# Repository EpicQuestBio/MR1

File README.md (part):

# MR1 Nanopore Reader (MR1)

[-brightgreen.svg)](#testing--verification)

The **MR1 Nanopore Reader** is an open-source, ultra-low-noise solid-state and biological nanopore sequencer flow cell, low-current transimpedance amplifier, and automated fluidic control system. It integrates high-precision parametric CAD models (`build123d`), ultra-low-leakage analog front-end electronics (KiCad), an automated dual-pump fluidic handler, and an ESP32-S3 high-speed continuous streaming firmware stack.

## Architecture & Overview
The system uses a complete **4-electrode topology** (Working Electrode `WE_POS` / `>PORE_AMP`, Working Sense `WS_CIS` & `WS_CIS_WIDE`, Reference Electrode `RE_TRANS`, Counter Electrode `CE_GNDA`) combined with explicitly driven guards (`GUARD`, `GUARD_WIDE`, `GUARD_CIS_A`, `GUARD_CIS_B`) across a distributed 12-pin interface ($36\text{ mm}$ span) to achieve sub-picoampere sensitivity, neutralize stray capacitance, and distribute mechanical spring forces across the PTFE substrate.

The architecture consists of:
- **Headstage Hardware**: A custom, low-parasitic PTFE/Rogers interposer cartridge that seats a 4x4mm nanopore wafer clamped within silicone PDMS gaskets. It interfaces via gold-plated pogo pins to a low-bias-current transimpedance amplifier (LMP7721) mounted beneath the flowcell.
- **Reader Hardware (MR1)**: An ESP32-S3-driven core processing node operating a continuous 100 kHz SPI DMA data acquisition sequence, dual DACs for precision transmembrane voltage bias, and USB CDC-ACM streaming logic.
- **Pump / Power Subsystem**: A dedicated USB-PD powered board managing automated fluidic dispensing (peristaltic motors), pressure sensing, and SBU-based I2C communication back to the main MR1 host.
- **Data Ingestion Pipeline**: High-throughput IPC software utilizing python scripts (`daq_client.py`) and zeroMQ / WebSocket endpoints to reliably process, structure, decode, and log the real-time electrical data for machine learning basecalling or browser visualization.

## Setup & Prerequisites
To build, modify, or interact with this repository, ensure your environment meets these requirements.

### Toolchain Prerequisites
- **Python**: 3.10+
- **KiCad**: Version 7.0+ (For PCB design modifications and scripting exports)
- **PlatformIO Core (CLI)**: For firmware compilation (`pio run`)
- **OpenSCAD / build123d**: For generating solid body parts.
- **Node.js**: v18+ (For UI and test automation dependencies)

### Environment Setup
Run the bootstrap setup scripts depending on your OS to establish a clean python virtual environment and node module cache.
```bash
# On Linux/macOS
./setup_env.sh

# On Windows (PowerShell)
.\setup_env.ps1
```

Activate the python virtual environment:
```bash
source .venv/bin/activate
```

### Build & Test
You can trigger the comprehensive unit, integration, and dimension-parity tests using the included test suite.
```bash
# Ensure you have activated the virtual environment and built assets
python run_tests.py
# Or directly via pytest
pytest tests/
```

To build and upload firmware to the MR1 reader or the Pump board:
```bash
# Navigate to the target directory
cd MR1_firmware  # or cd Pump_firmware
pio run --target upload
```

## License

This project is dedicated to the public domain under the **CC0 1.0 Universal (CC0 1.0) Public Domain Dedication**.

Created by Lawrence R. Kincheloe III / Molecular Reality Corp (2026).
See the `LICENSE` file for the full text.

---

## Table of Contents

- [Architecture & Overview](#architecture--overview)
- [Setup & Prerequisites](#setup--prerequisites)
- [License](#license)
- [System Architecture](#system-architecture)
- [Project Structure](#project-structure)
- [Quick Start & Environment Setup](#quick-start--environment-setup)
- [Deliverables & Export System](#deliverables--export-system)
- [Hardware Build Pipeline & Board Status](#hardware-build-pipeline--board-status)
- [OpenAuto-CFD & Co-Design](#openauto-cfd--co-design)
- [3D Visualizer & Interactive Inspection](#3d-visualizer--interactive-inspection)
- [KiCad Action Plugin & CLI](#kicad-action-plugin--cli)
- [Testing & Verification](#testing--verification)
- [Hardware & Electronics](#hardware--electronics)
- [ESP32-S3 Firmware](#esp32-s3-firmware)
- [Fluidic Routing & Mold Casting](#fluidic-routing--mold-casting)
- [Documentation Index](#documentation-index)

## System Architecture

```
                       +---------------------------------------+
                       |           Host PC / Laptop            |
                       |  (High-Throughput Binary Telemetry)   |
                       +-------------------+-------------------+
                                           | J1_HOST (USB-C Cable: USB-PD Sink + High-Speed Data)
                                           v
                       +---------------------------------------+
                       |      Pump Module Board (Pump/)        |
                       |  - STUSB4500 Autonomous USB-PD Sink   |
                       |  - TS3USB221 USB 2.0 Streaming Pass   |
                       |  - STM32G431 Control MCU @ 170 MHz    |
                       |  - Dual Honeywell ABP2 Pressure Sens  |
                       |  - Dual DRV8837C Peristaltic Drivers  |
                       |  - Clean Regulated 5V Output Filter   |
                       +-------------------+-------------------+
                                           | J2_MR1 (USB-C Link: +5V_MR1_CLEAN + SBU I2C + USB)
                                           v
                       +---------------------------------------+
                       |         ESP32-S3 MCU (MR1)            |
                       |  Core 1: ADC SPI DMA & USB CDC Stream |
                       |  Core 0: Web Server, Leak & Pump Ctrl |
                       +---------+-------------------+---------+
                                 |                   |
            SPI Bus (100 kHz)    |                   | UART (J22) / SBU I2C
                                 v                   v
     +-----------------------------+        +--------------------------+
     |     AD40xx 16/18-Bit ADC    |        |  Dual Peristaltic Pumps  |
     |   LMP7721 Ultra-Low-Noise   |        |  (Cis & Trans Chambers)  |
     |     Cartridge Amplifier     |        +--------------------------+
     +--------------+--------------+
                    | Gold Pogo Pins (Ultra-low noise shielded)
                    v
     +---------------------------------------------------------+
     |              Hexagonal Cartridge Flow Cell              |
     |  - Cis & Trans Fluidic Chambers ('X' microfluidic)      |
     |  - Cast Silicone Gasket with Nanopore Silicon Wafer     |
     |  - M75x8mm Clamping Torque Cap & Pressure Puck          |
     |  - Conductive Weep Moat / Leak Detection Sensor         |
     +---------------------------------------------------------+
```

---

## Project Structure

```
mr1/
├── src/                          # Parametric CAD models (build123d / Python)
│   ├── cartridge.py              # Flow cell cartridge stack & PCB models
│   ├── housing.py                # Reader and Pump housings, lids, mounting
│   ├── nanopore_wafer_mold.py    # Interlocking two-part resin casting mold
│   ├── torque_cap.py             # M75/M76 ratcheting torque limiter cap
│   ├── adapters.py               # Luer-lock and threaded NPT fluidic adapters
│   ├── connectors.py             # USB-C, JST XH, and bulkhead panel mounts
│   ├── assembly.py               # Full 3D assembly & 3D spline routing sweeps
│   ├── collision_check.py        # Automated 3D BREP collision & clearance checker
│   └── constants.py              # Central engineering & physical parameters
├── MR1/                          # KiCad 10.0 project for Main Reader Board (4-Layer)
├── Amplifier/                    # KiCad 10.0 project for Cartridge Transimpedance Amp (2-Layer)
├── Pump/                         # KiCad 10.0 project for Pump Controller & USB-PD Hub (4-Layer)
├── MR1_firmware/                 # ESP32-S3 C++ firmware (PlatformIO)
│   ├── include/                  # Pinout mapping, binary protocol framing, web portal
│   ├── src/hal/                  # AD40xx SPI DMA ADC, MCP4822 DAC, Leak Detector
│   ├── src/comm/                 # High-speed USB CDC streaming & UART Pump protocol
│   └── src/web/                  # Embedded Web Portal with WebSocket Oscilloscope
├── wiring/                       # WireViz electrical and fluidic harness specs
│   ├── reader_wiring.yaml        # USB-C, motor, and analog pogo wiring harnesses
│   └── reader_tubing.yaml        # FEP, PharMed BPT, and silicone fluidic tubing specs
├── tests/                        # Automated unit, CAD bounds, firmware, and E2E tests
│   ├── test_geometry.py          # Geometric validity and collision regression
│   ├── test_golden_stl_bounds.py # Dimensional assertions against golden models
│   ├── test_connector_bounds.py  # Connector mounting dimensional checks
│   ├── test_firmware_protocol.py # Binary framing, CRC-16, and DAC mapping tests
│   └── test_exports_e2e.py       # Full deliverables validation (141 files)
├── scripts/                      # Build, export, and testing automation
│   ├── export_manager.py         # Universal multi-domain export orchestrator
│   ├── export_all.sh             # POSIX bash export runner
│   └── run_e2e_tests.sh          # POSIX bash end-to-end test runner
├── exports/                      # Generated release deliverables & manifest
├── requirements.txt              # Pinned Python virtual environment dependencies
├── setup_env.sh                  # Virtual environment manager (Linux/macOS/Bash)
├── setup_env.ps1                 # Virtual environment manager (Windows PowerShell)
├── Makefile                      # Standard project build and export targets
├── EXPORTS.md                    # Detailed deliverables and ordering documentation
├── BOM.md                        # Mechanical bill of materials & sourcing links
└── CASTING.md                    # PDMS/Silicone flow cell casting guidelines
```

---

## Quick Start & Environment Setup

### 1. Initialize Python Virtual Environment

The project uses a local virtual environment (`.venv`) for all Python CAD generation, export pipelines, and test suites.

**On Windows (PowerShell):**
```powershell
.\setup_env.ps1
```

**On Linux / macOS / Git Bash:**
```bash
chmod +x setup_env.sh install.sh
./setup_env.sh
```

To verify environment health at any time:
```bash
./setup_env.sh --check        # or powershell -File .\setup_env.ps1 -Check
```

### 2. Required External Tools (Optional for specific export domains)
- **KiCad 10.0 CLI** (`kicad-cli`): Required to generate Gerbers, Drill files, Pick & Place CSVs, BOMs, and PDF schematics.
- **Graphviz** (`dot`): Required by WireViz for rendering graphical wiring and tubing diagrams.
- **PlatformIO Core** (`pio`): Required to compile ESP32-S3 firmware binaries.

---

## Deliverables & Export System

The repository features an automated multi-domain export orchestrator (`scripts/export_manager.py`) managed via GNU Make, shell scripts, or npm:

### Common Commands

```bash
# Export all project deliverables (CAD, KiCad, Wiring, Firmware, and Manifest)
make export

# Or export specific domains
make export-cad        # 3D Solids (STEP/STL) & 2D CNC Profiles (DXF)
make export-kicad      # Gerbers, Drill, POS, BOM, and PDF schematics
make export-wiring     # WireViz wiring harness and fluidic diagrams
make export-firmware   # Compile and stage ESP32-S3 firmware binaries

# Verify manifest and deliverables
make check             # Verify all 141 indexed deliverables exist on disk
make test              # Run unit tests and CAD collision clearance checks
make test-e2e          # Run end-to-end deliverables validation test
```

### Generated Deliverables Inventory (`exports/`)
- **30 STL Meshes**: Ready for 3D printing (SLA resin molds, TPU pusher plates, PETG housings, and PTFE interposer models).
- **22 STEP Models**: Parametric BREP solids for mechanical assembly and CAD exchange.
- **13 DXF Profiles**: 2D profiles for CNC milling polypropylene sheet stock and synchronizing KiCad PCB `Edge.Cuts` (including `Interposer_DXF.dxf` and `Plate_2_Channel_DXF.dxf`).
- **Fab-Ready PCB Archives**: `MR1_Gerbers.zip` (4-layer main board) and `Amplifier_Gerbers.zip` (2-layer amplifier).
- **Manufacturing Documentation**: Pick-and-Place (POS) coordinates, BOM CSVs, and multi-sheet schematic PDFs.
- **Harness Documentation**: WireViz diagrams for internal wiring and 1/8" barb fluidic tubing.
- **ESP32-S3 Firmware**: Staged `firmware.bin`, `bootloader.bin`, and `partitions.bin`.
- **SHA-256 Manifest**: `exports/manifest.json` tracks file sizes and cryptographic hashes for all 159 files for drift detection.

See [EXPORTS.md](EXPORTS.md) for full details and PCB fabrication recommendations.

---

## Hardware Build Pipeline & Board Status

Automated code scanners and reviewers sometimes mistake the repository's PCB source files for static production-ready layouts. The MR1 hardware design pipeline relies on two fundamental principles:

1. **Dynamic Artifact Generation**:
   The `.kicad_pcb` layout files and downstream fabrication deliverables (Gerber layers, NC drill files, BOMs, Pick and Place POS files, multi-sheet PDF schematics) are dynamically generated and reconciled via the repository's automation pipeline (`scripts/export_manager.py`, Python footprint/layout generators, and `kicad-cli`), rather than being maintained as static hand-edited binaries in the working tree.

2. **Current Board Layout & Routing Status**:
   - **`MR1` Main Reader Board** (`MR1/`): 111 footprints placed, placement complete, 0 routed copper tracks.
   - **`Amplifier` Cartridge Board** (`Amplifier/`): 48 footprints placed, placement complete, 0 routed copper tracks.
   - **`Interposer` Microfluidic Board** (`Interposer/`): 33 footprints placed, 9 routed segments.
   - **`Pump` Controller Board** (`Pump/`): 18 footprints placed, procedurally generated stubs — STM32 QFN-48 currently a 1-pad stub with passives and 3D models pending per [`TODO.md`](TODO.md) §22.

For details on Gerber archiving, dynamic export workflows, and hardware version tags, see the [Artifact & Gerber Release Policy in EXPORTS.md](EXPORTS.md#artifact--gerber-release-policy).

---

## OpenAuto-CFD & Co-Design

The **MR1 Nanopore Reader** incorporates the **OpenAuto-CFD** co-design framework ([`openauto.project.json`](openauto.project.json) / [`atlas.project.json`](atlas.project.json)) to bridge Electrical CAD (KiCad), Mechanical CAD (Build123d / OpenSCAD), and Microfluidic Multiphysics into a single automated pipeline.

### Why OpenAuto-CFD?
Nanopore sensing demands precise hydrodynamic and electro-chemical alignment:
1. **Laminar Stokes Flow ($\text{Re} \ll 1$):** With $50\,\mu\text{m} \times 25\,\mu\text{m}$ channels and $10\,\mu\text{L/min}$ delivery, OpenAuto-CFD calculates viscous pressure drops ($\Delta P \approx 6.2\text{ kPa}$) and eliminates turbulent vortex formation.
2. **SiN Membrane Burst Safety:** Free-standing $20\text{ nm}$ silicon nitride membranes rupture at differential pressures $\Delta P_{\text{burst}} \sim 10\text{ mbar}$. OpenAuto-CFD co-simulation balances hydrodynamic resistance across Cis and Trans chambers to prevent wafer fracture.
3. **Dead-Volume & Bubble Prevention:** Eliminates stagnation recirculation zones ($\vec{v} < 0.01 \cdot v_{\text{bulk}}$) that trap air microbubbles or cause analyte sample carryover.
4. **Concentric Kelvin Cell Coupling:** Aligns the 4-electrode Kelvin sensing array on the PTFE interposer directly with the microfluidic chamber aperture.

See the comprehensive [OpenAuto-CFD Guide](docs/OPENAUTO_CFD.md) for full physical derivations and co-simulation specs.

---

## 3D Visualizer & Interactive Inspection

The repository provides a rich multi-layer 3D visualizer powered by `build123d` and `ocp_viewer`:

```bash
# Launch interactive 3D assembly visualizer
npm run visualize
# Or via Python directly:
python src/assembly.py

# Or launch via install script diagnostic flag:
./install.sh --viewer
```

### Visualizer Features
- **Full System Assembly:** Displays the Peristaltic Pump base module, Reader Housing & Tower, 4× Luer Bulkhead Panel Mounts, 7-layer Cartridge Stack (Bottom Pusher Plate, Base Hex Plate, Fitted Gasket, Active PCB, Wafer Gasket, Top Hex Plate, Pressure Puck), and Torque-Lock Cap.
- **3D Swept Tubing Routes:** Renders actual 3D splines for all 5 fluidic paths (`TUBE_PUMP`, `TUBE_FEED`, `TUBE_TRANS_LINE`, `TUBE_WASTE_1`, `TUBE_WASTE_2`) with verified bend radii.
- **X-Ray & Clipping Plane Inspection:** Enables cross-sectional slicing to verify internal gasket compression and pogo pin deflection.
- **WireViz Electrical & Tubing Harnesses:** Generates SVG and HTML diagrams for internal wiring (`wiring/reader_wiring.yaml`) and fluid lines (`wiring/reader_tubing.yaml`) via `npm run export:wiring`.
- **Automated 360° Flythrough Video:** Renders photorealistic rotating orbits using PyVista VTK via `npm run render:flythrough`.

---

## KiCad Action Plugin & CLI

The repository includes a dedicated KiCad Action Plugin and CLI verification engine ([`plugins/openauto_cfd_plugin.py`](plugins/openauto_cfd_plugin.py)) ensuring PCB layouts strictly comply with mechanical, fluidic, and manifest constraints.

### How to Install the Plugin into KiCad
```bash
# Install plugin into active KiCad installation (~/.local/share/kicad/ or %APPDATA%/kicad/)
npm run openauto:install-plugin
# Or via Python:
python plugins/openauto_cfd_plugin.py --install
```

### Using Inside KiCad PCB Editor (GUI)
1. Open any board (`Amplifier.kicad_pcb`, `MR1.kicad_pcb`, `Pump.kicad_pcb`, or `Interposer.kicad_pcb`).
2. Navigate to **Tools $\to$ External Plugins $\to$ OpenAuto-CFD: Co-Design & Clearance Verifier**.
3. The plugin parses the board, checks Edge.Cuts continuity, verifies bounding dimensions against `openauto.project.json`, and displays a comprehensive verification report.

### Standalone CLI & CI/CD Verification
```bash
# Validate all 4 boards in headless mode (Edge.Cuts continuity, dimensions, and net mapping)
npm run openauto:validate

# Synchronize Edge.Cuts dimensions back into the openauto.project.json manifest
npm run openauto:sync
```

---

## Testing & Verification

The project enforces zero physical interference and strict dimensional fidelity across all hardware interfaces:

```bash
# Run the complete test suite (Unit Tests, Collision Checks, Firmware Protocol, Parity, and E2E)
python run_tests.py
```

### Automated Validation Includes:
1. **Golden STL & PCB Bounds**: Asserts dimensions of all generated CAD models against benchmark constraints.
2. **BREP Collision Clearance (6 Independent Suites)**:
   - Cartridge stack component alignment.
   - Housing and lid clearances.
   - M75×8mm external / M76×8mm internal helical thread engagement (0 interference volume).
   - PCB standoff clearances against fluidic lines.
   - Internal component clearance (wiring vs. cartridge solids).
   - Flexible routing collision sweeps against module envelopes.
3. **Spline Bend Radius Validation**: Computes instantaneous curvature along swept routes and verifies compliance with minimum bend radii (Silicone/FEP tubing $\ge 10\text{ mm}$, Wiring $\ge 10\text{ mm}$).
4. **CAD Feature Validation Suite**: Validates 80x60mm rectangular motherboard, hexagonal carrier frame, circular nanopore carrier, mold modes, lid cutouts, and pump case bosses.
5. **Firmware Protocol Tests**: CRC-16 integrity, binary packet serialization (`StreamFrame`), pump packet XOR checksums, and DAC voltage-to-code mapping.
6. **E2E Deliverables Tests**: Validates headers, non-zero file sizes, and SHA-256 hashes of all 159 export deliverables.

---

## Hardware & Electronics

- **MR1 Main Controller Board** (`MR1/`):
  - 4-Layer stackup:
    - Layer 1 (Top Signal): Component placement, USB D+/D-, SPI traces to FPC, DAC outputs
    - Layer 2 (Ground Plane): Split into GNDA (Quiet Analog Ground) and GND (Digital Ground)
    - Layer 3 (Power Plane): Split into Analog Power (VDDA, VSSA) and Digital Power (+3V3, VBUS)
    - Layer 4 (Bottom Signal): Secondary routing, low-speed housekeeping, and auxiliary pours
  - ESP32-S3-MINI-1U MCU with native high-speed USB CDC.
  - Dedicated SPI bus for high-speed ADC sampling.
  - Dual MCP4822 12-bit DACs providing bipolar pore bias voltages (-1.587V to +1.587V) and unblocking pulses.
  - Conductive weep-hole leak detection sensing on GPIO1.
- **PTFE Interposer Circuit Board** (`Interposer/` & `src/cartridge.py`):
  - 55.0 × 51.962 × 0.8 mm hexagonal substrate fabricated on ultra-low-loss PTFE / Rogers RO4350B.
  - Physical and electrical barrier dividing Cis (top) and Trans (bottom) microfluidic chambers.
  - Dual-sided silver chloride (Ag/AgCl) ribbon electrode pads positioned inside the Cis ($30^\circ$) and Trans ($210^\circ$) flow channels.
  - Central 6.20 × 6.20 mm diamond cutout ($45^\circ$) allowing the silicone gasket protrusion to seal directly around the silicon nanopore wafer.
  - 12-pin guarded ENIG landing array (`PogoPin_Target_12Pin_Distributed`) flanking high-impedance sense lines (`WS_CIS`, `RE_TRANS`) with driven low-impedance `GUARD` pins.
  - Hermetically clamped between `Cast_Nanopore_Wafer_Gasket` (top) and `Fitted_Amplifier_Gasket` (bottom).
- **Cartridge Transimpedance Amplifier** (`Amplifier/`):
  - 2-Layer 0.8 mm ultra-thin board designed for direct insertion into the flow cell stack.
  - LMP7721 ultra-low input bias current amplifier (sub-femtoampere leakage).
  - Low-leakage guard rings and driven shields guarding the high-impedance nanopore input node.
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
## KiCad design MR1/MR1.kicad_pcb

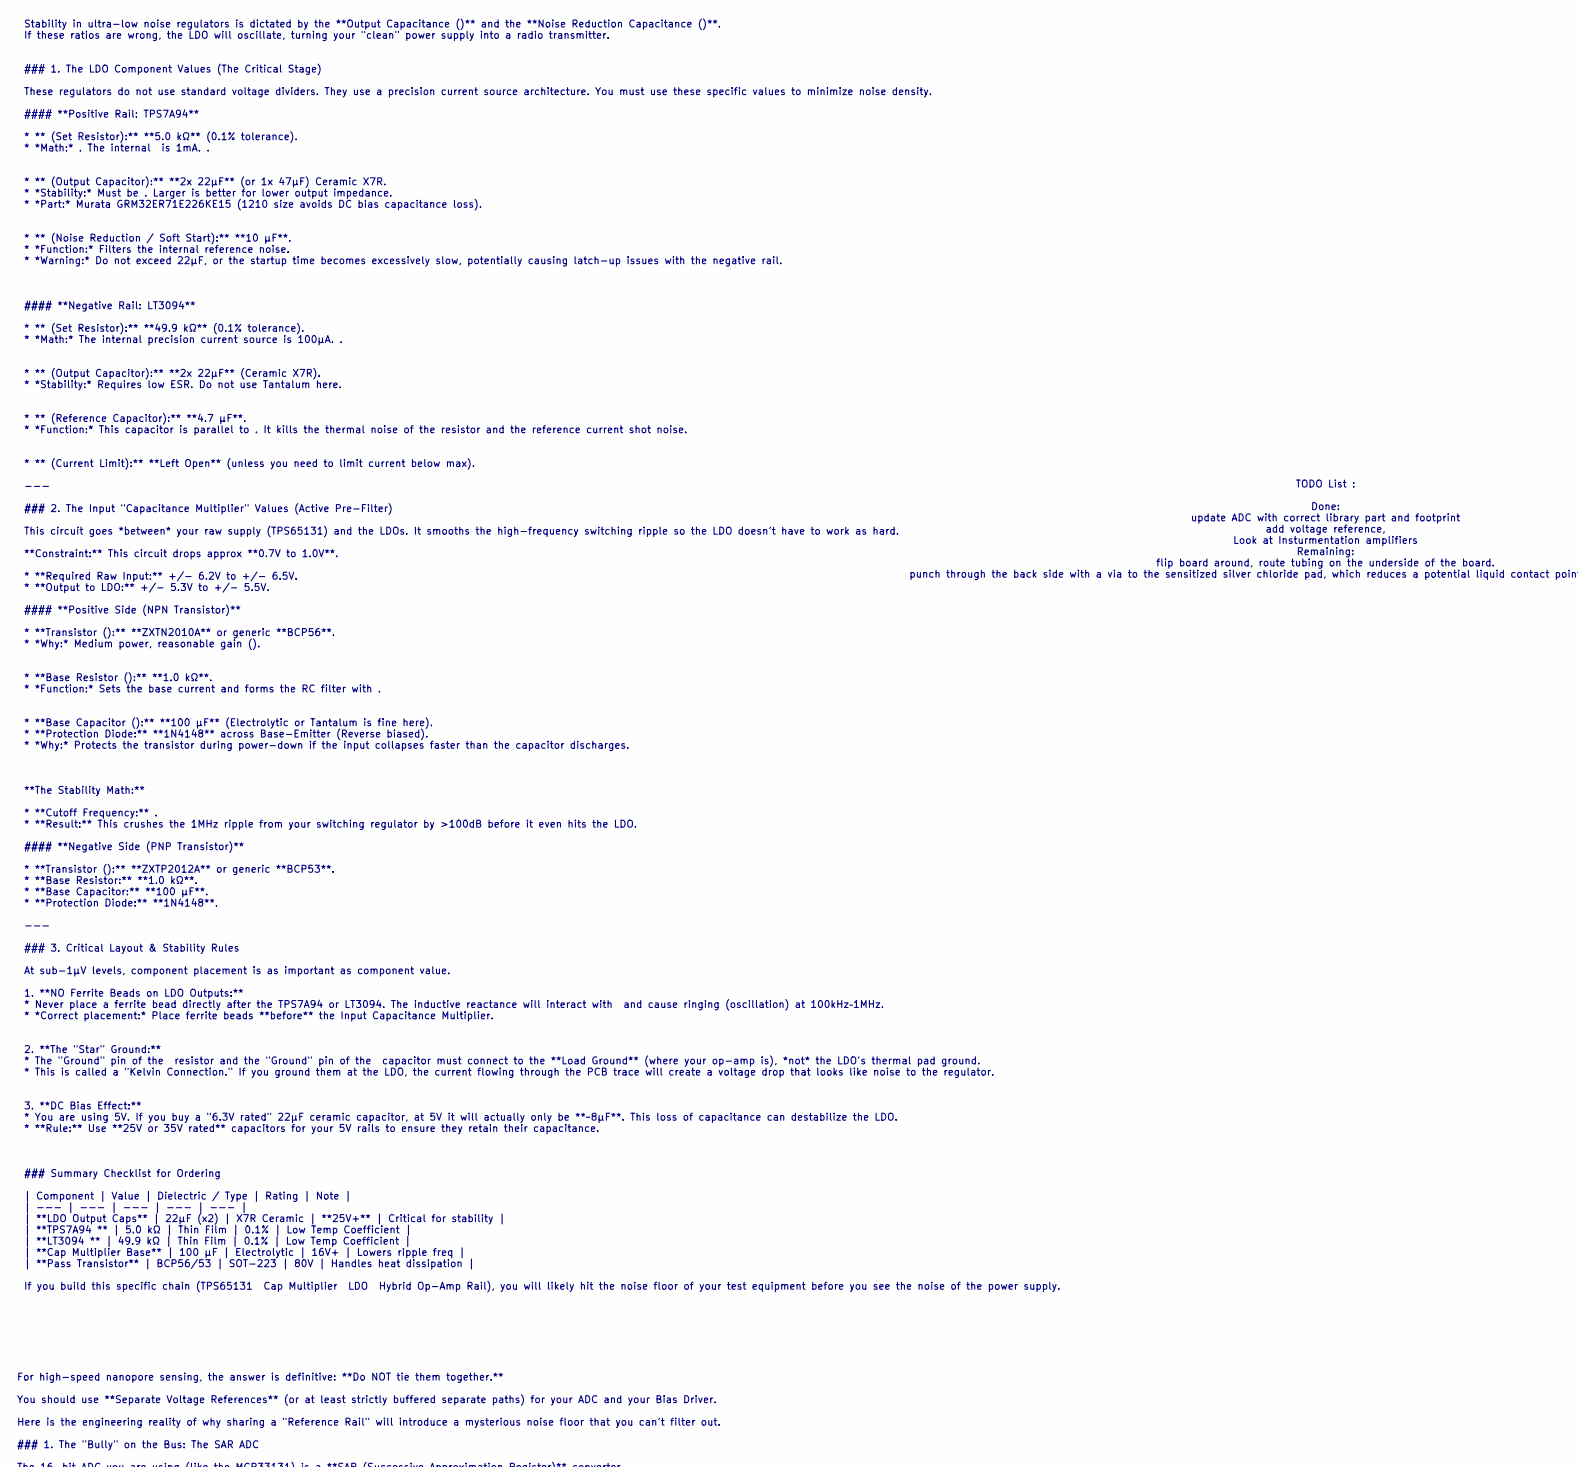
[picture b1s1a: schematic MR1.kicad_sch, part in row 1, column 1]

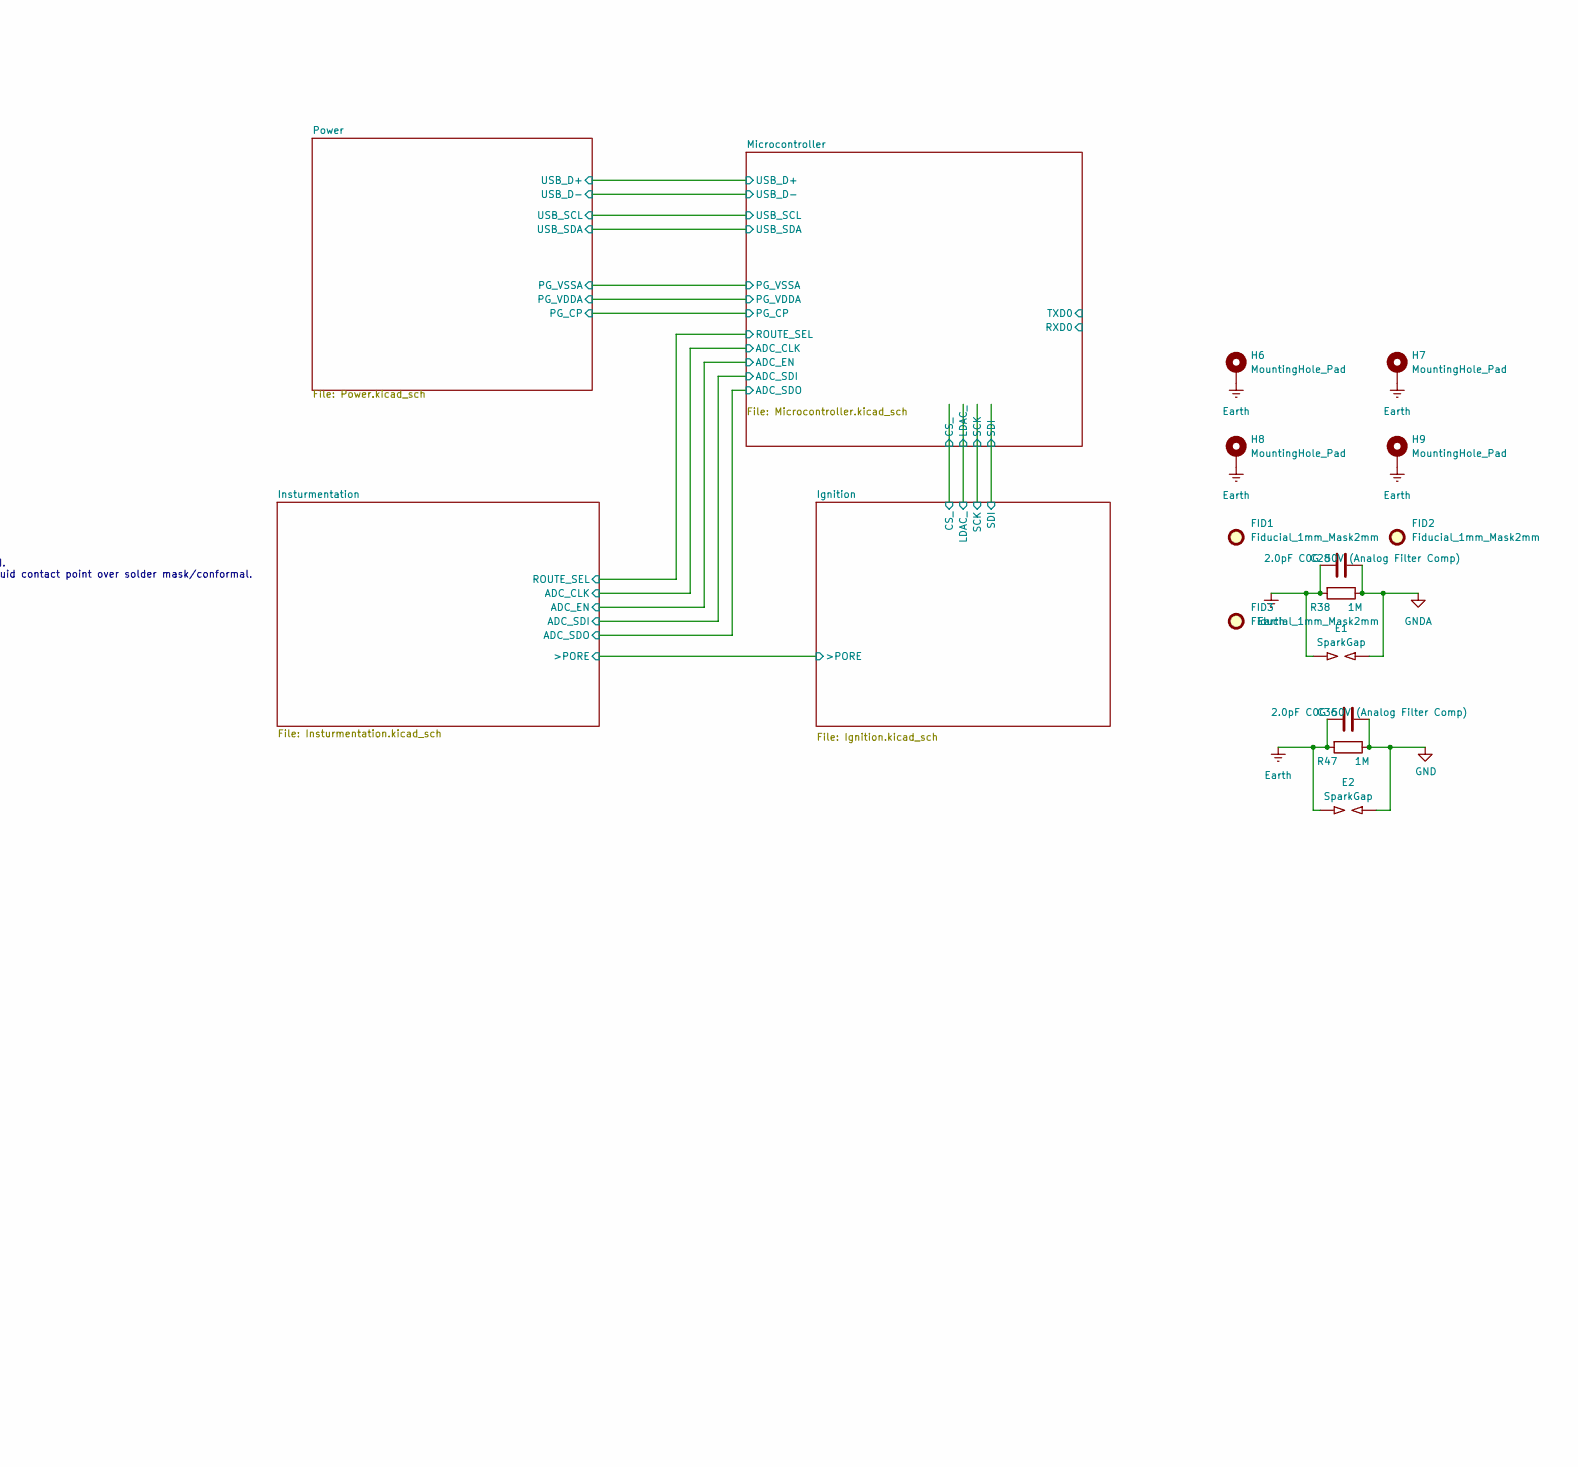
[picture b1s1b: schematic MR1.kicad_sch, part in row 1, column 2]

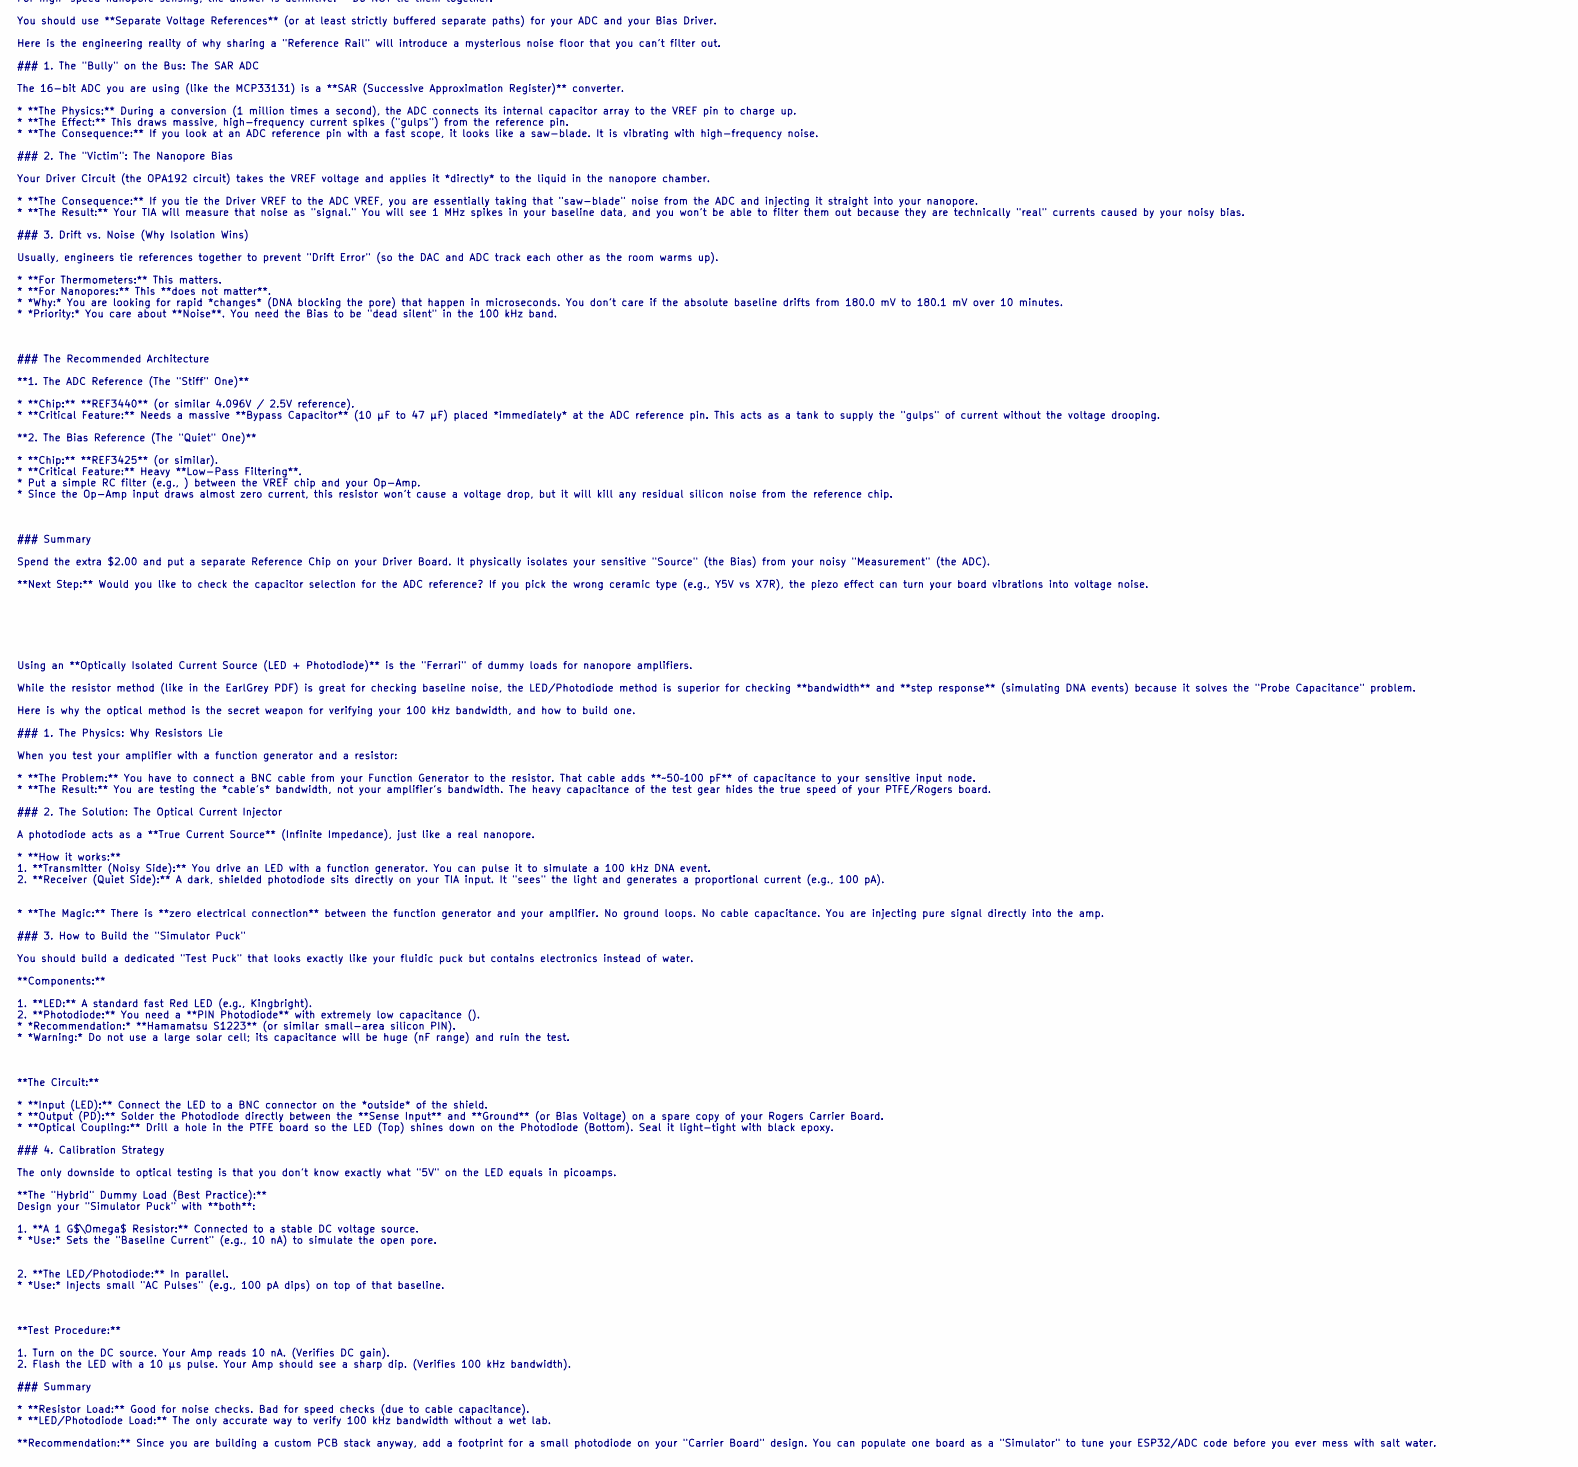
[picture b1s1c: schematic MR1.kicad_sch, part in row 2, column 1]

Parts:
C28, C36: 2.0pF C0G 50V (Analog Filter Comp); C_0402_1005Metric; LCSC C161316
E1, E2: SparkGap; SolderJumper-2_P1.3mm_Open_TrianglePad1.0x1.5mm
FID1, FID2, FID3: Fiducial_1mm_Mask2mm
H6, H7, H8, H9: MountingHole_Pad; MountingHole_3.2mm_M3_Pad_Via
R38, R47: 1M; R_0402_1005Metric; LCSC C26083

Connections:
Earth: C28.2, C36.2, E1.1, E2.1, H6.1 (1_1), H7.1 (1_1), H8.1 (1_1), H9.1 (1_1), R38.2, R47.2; also elsewhere on the board
GND: C36.1, E2.2, R47.1; also elsewhere on the board
GNDA: C28.1, E1.2, R38.1; also elsewhere on the board

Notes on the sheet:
Stability in ultra-low noise regulators is dictated by the **Output Capacitance ()** and the **Noise Reduction Capacitance ()**. If these ratios are wrong, the LDO will oscillate, turning your "clean" power supply into a radio transmitter. ### 1. The LDO Component Values (The Critical Stage) These 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
For high-speed nanopore sensing, the answer is definitive: **Do NOT tie them together.** You should use **Separate Voltage References** (or at least strictly buffered separate paths) for your ADC and your Bias Driver. Here is the engineering reality of why sharing a "Reference Rail" will introduce 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
TODO List : Done: update ADC with correct library part and footprint add voltage reference, Look at Insturmentation amplifiers Remaining: flip board around, route tubing on the underside of the board. punch through the back side with a via to the sensitized silver chloride pad, which reduces a pote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
Using an **Optically Isolated Current Source (LED + Photodiode)** is the "Ferrari" of dummy loads for nanopore amplifiers. While the resistor method (like in the EarlGrey PDF) is great for checking baseline noise, the LED/Photodiode method is superior for checking **bandwidth** and **step response*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

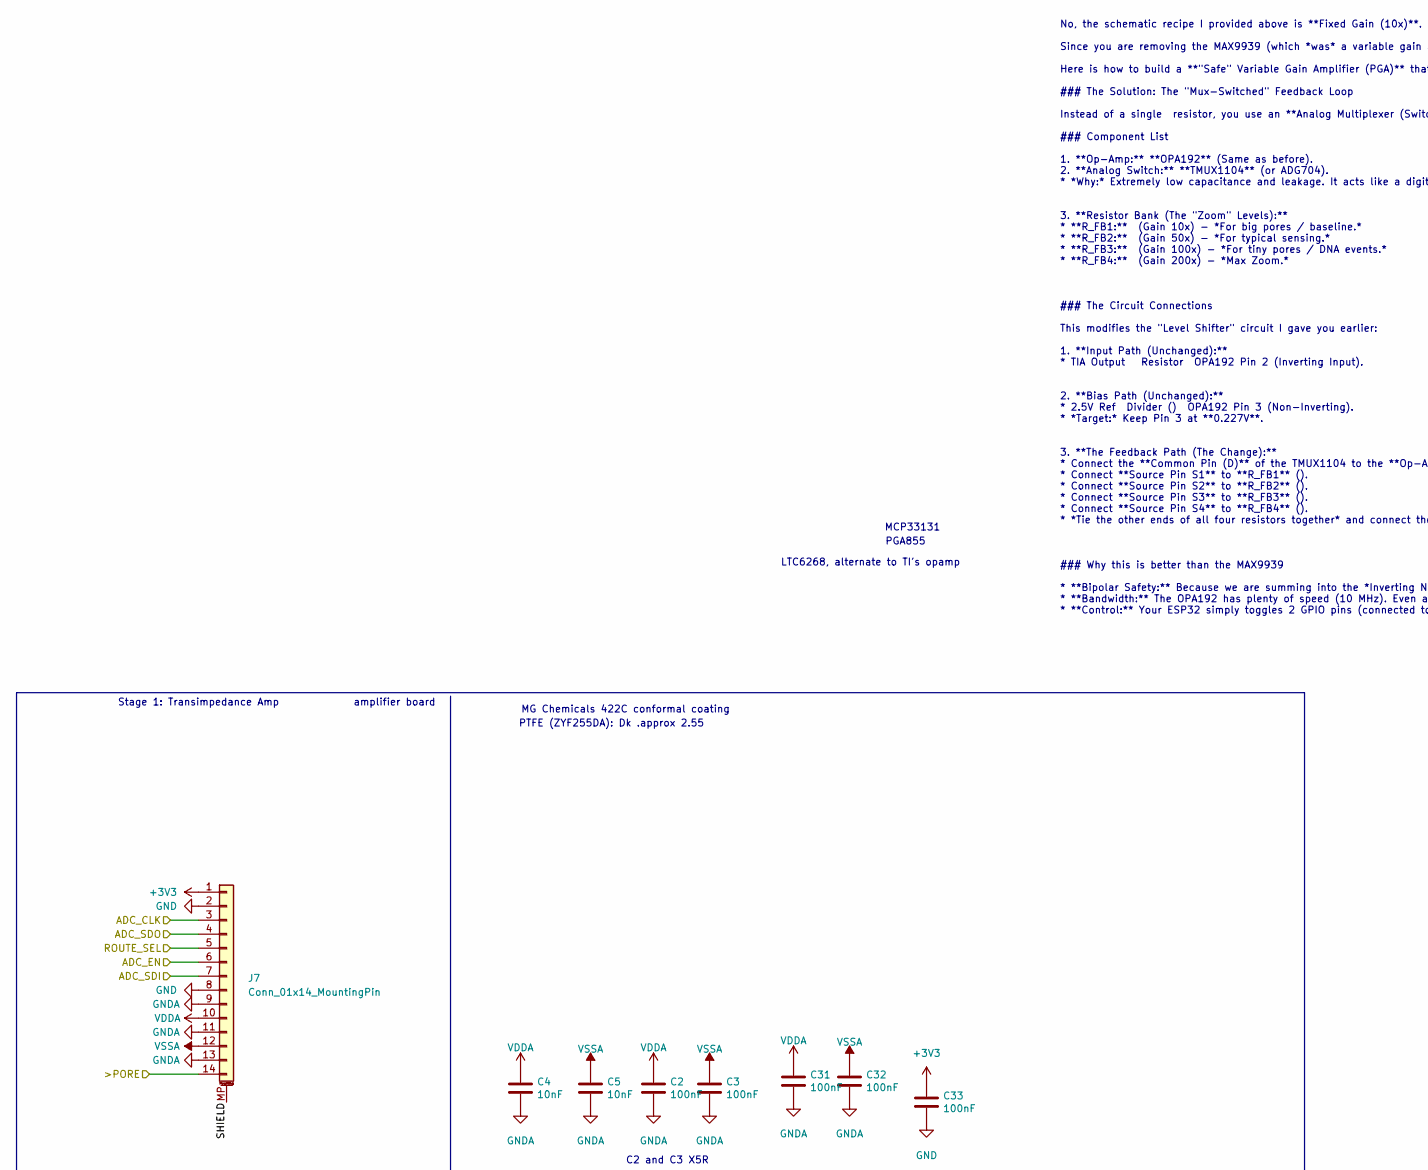
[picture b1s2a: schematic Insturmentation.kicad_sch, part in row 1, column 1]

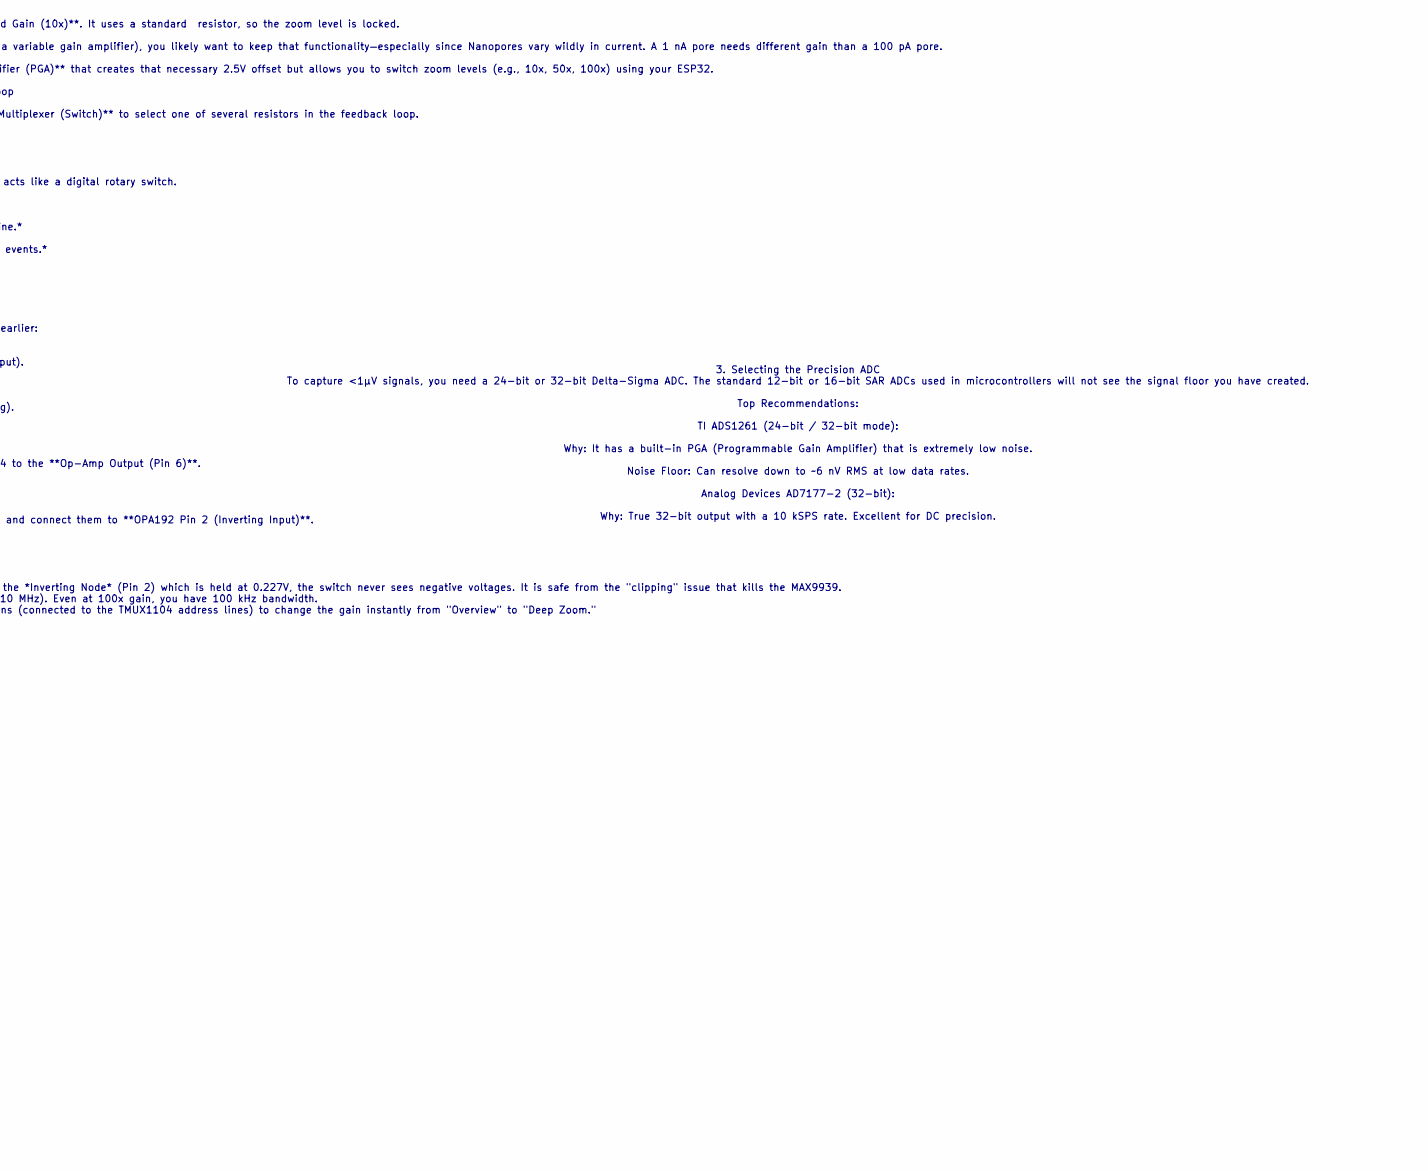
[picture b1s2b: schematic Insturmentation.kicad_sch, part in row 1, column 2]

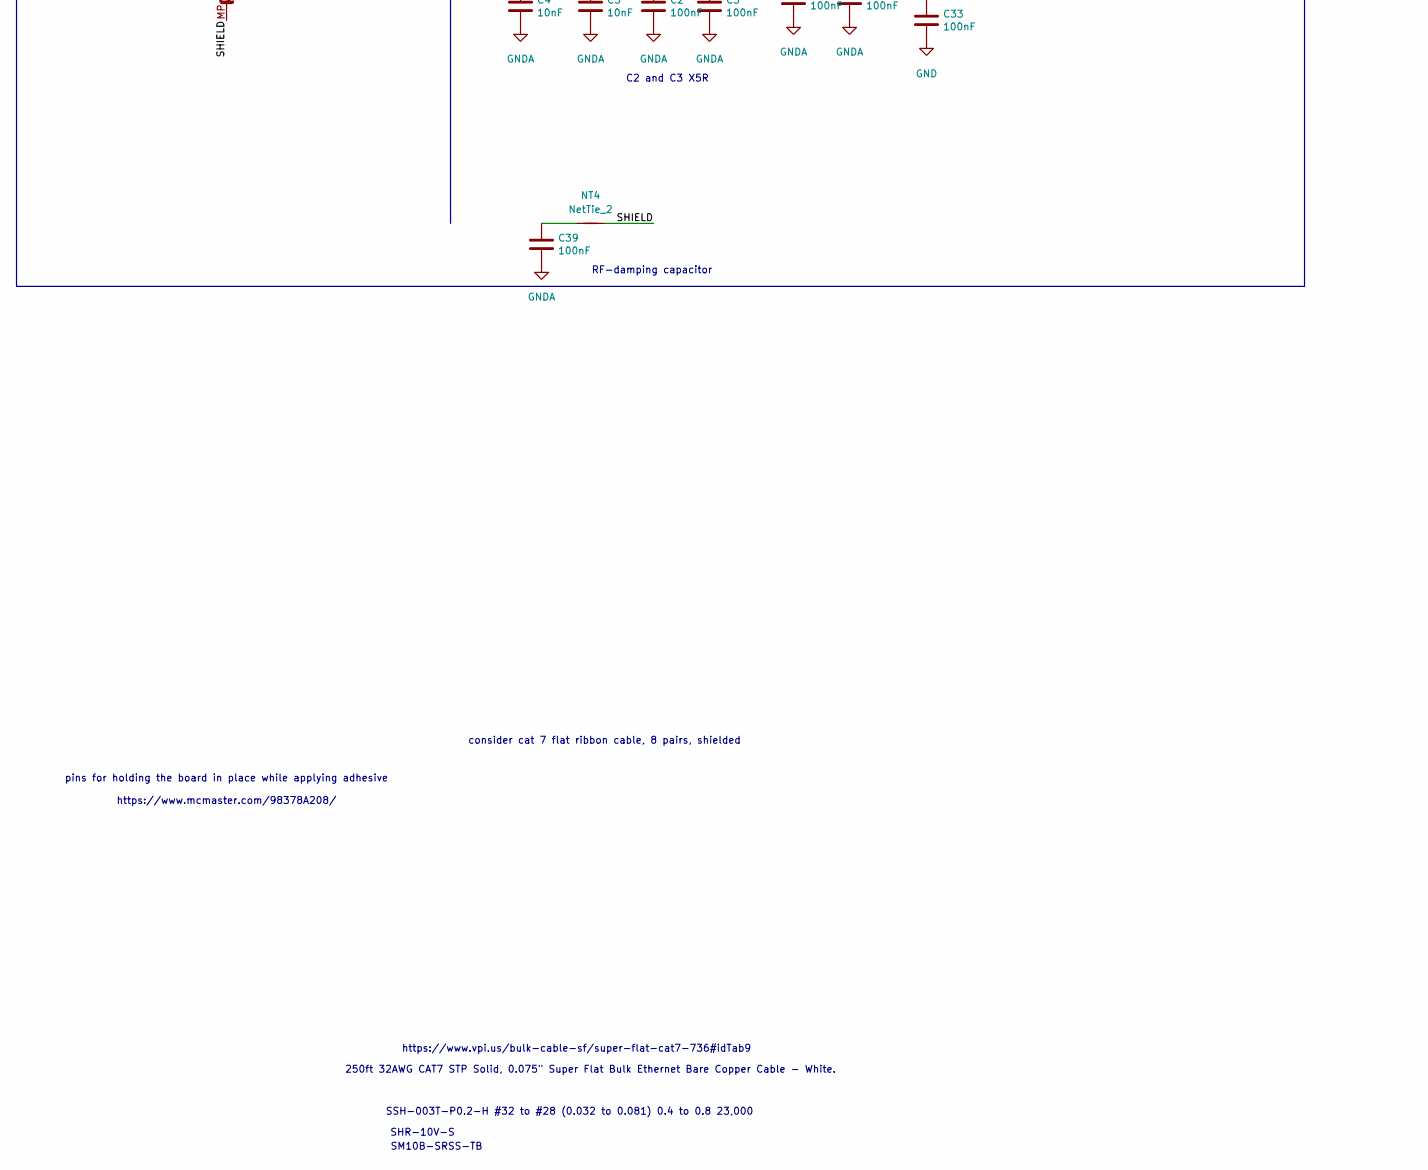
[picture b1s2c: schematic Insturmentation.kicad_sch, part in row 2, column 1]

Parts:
C2, C3, C31, C32, C33, C39: 100nF; C_0402_1005Metric; LCSC C1525
C4, C5: 10nF; C_0402_1005Metric; LCSC C15195
J7: Conn_01x14_MountingPin; Amphenol_F32R-1A7x1-11014_1x14-1MP_P0.5mm_Horizontal; LCSC C2856818
NT4: NetTie_2; NetTie-2_SMD_Pad0.5mm

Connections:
+3V3: C33.1, J7.1; also elsewhere on the board
/Ignition/>PORE: J7.14; also elsewhere on the board
/Insturmentation/ADC_CLK: J7.3; also elsewhere on the board
/Insturmentation/ADC_EN: J7.6; also elsewhere on the board
/Insturmentation/ADC_SDI: J7.7; also elsewhere on the board
/Insturmentation/ADC_SDO: J7.4; also elsewhere on the board
/Insturmentation/ROUTE_SEL: J7.5; also elsewhere on the board
/Insturmentation/SHIELD: J7.MP (MountPin), NT4.2
GND: C33.2, J7.2, J7.8; also elsewhere on the board
GNDA: C2.2, C3.2, C4.2, C5.2, C31.2, C32.2, C39.2, J7.9, J7.11, J7.13; also elsewhere on the board
unnamed: C39.1, NT4.1
VDDA: C2.1, C4.1, C31.1, J7.10; also elsewhere on the board
VSSA: C3.1, C5.1, C32.1, J7.12; also elsewhere on the board

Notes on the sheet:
consider cat 7 flat ribbon cable, 8 pairs, shielded
pins for holding the board in place while applying adhesive https://www.mcmaster.com/98378A208/
C2 and C3 X5R
PGA855
https://www.vpi.us/bulk-cable-sf/super-flat-cat7-736#idTab9
SM10B-SRSS-TB
PTFE (ZYF255DA): Dk .approx 2.55
amplifier board
No, the schematic recipe I provided above is **Fixed Gain (10x)**. It uses a standard resistor, so the zoom level is locked. Since you are removing the MAX9939 (which *was* a variable gain amplifier), you likely want to keep that functionality—especially since Nanopores vary wildly in current. A 1 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
Stage 1: Transimpedance Amp
MCP33131
MG Chemicals 422C conformal coating
250ft 32AWG CAT7 STP Solid, 0.075" Super Flat Bulk Ethernet Bare Copper Cable - White.
SHR-10V-S
LTC6268, alternate to TI's opamp
RF-damping capacitor
SSH-003T-P0.2-H #32 to #28 (0.032 to 0.081) 0.4 to 0.8 23,000
3. Selecting the Precision ADC To capture <1µV signals, you need a 24-bit or 32-bit Delta-Sigma ADC. The standard 12-bit or 16-bit SAR ADCs used in microcontrollers will not see the signal floor you have created. Top Recommendations: TI ADS1261 (24-bit / 32-bit mode): Why: It has a built-in PGA (Pr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

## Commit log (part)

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2025-12-23 Add Sentinel Nanopore Reader Rev 11 SCAD file
    - Create `sentinel_nanopore_reader.scad` with the provided Rev 11 design.
    - Optimize housing generation by replacing expensive `minkowski` sum with `linear_extrude` + `offset`.
    - Fix threading incompatibility between Housing and Torque Cap by unifying on BOSL2 `threaded_rod` with a 20mm pitch.
2025-12-23 Redesign housing as split Case/Lid, add feet/interposer
    - Split `Housing_3D` into `Housing_Case` (bottom bucket) and `Housing_Lid` (top plate) to improve 3D printability and allow for a sealed chamber.
    - Add 4x mounting feet to `Housing_Case` with M3 heat-set insert holes.
    - Integrate square `Interposer` module and update `Plate_2_Channel` pocket.
    - Refactor Housing and Cap to use BOSL2 attachments and primitives.
    - Restore internal mounts for Pump and PCB on the Case floor.
    - Standardize thread pitch to 20mm for Torque-Lock mechanism.
2025-12-23 Add support for 1/4 inch NPT compression fittings to Housing_Lid and introduce Bottom_Pusher_Plate
    - Modified `Housing_Lid` to replace the central cutout with a solid shelf.
    - Added 4x bosses on the underside of `Housing_Lid` with 1/4" NPT threads (approx).
    - Created `Bottom_Pusher_Plate` module (TPU) with O-ring seats for sealing.
    - Updated cartridge stack (`Plate_1`, `Plate_2`, `Plate_3`, `Gasket`) to support 4 fluid ports (Bottom Flush & Top Flush).
    - Updated port radius to 20mm and angles to ±30°/150°/210° to fit larger fittings.
    - Added `Bottom_Pusher_Plate_STL` to output options.
2025-12-24 adding json visuialization and e2e testing
2025-12-25 Correct BOSL2 attach coordinates for ports and connectors
    Fixed floating components and failing boolean operations by:
    1. Removing incorrect Z-axis offsets (`pump_h/2`, `lid_thick/2`) in `attach()` blocks that caused ports to detach from walls.
    2. Removing incorrect rotations (`rotate([0,90,0])`, `rotate([90,0,0])`) to ensure ports and cutouts align with the surface normal.
    3. Standardizing side port translations.
    This resolves issues with "ghost holes" (red cylinders) failing to cut the housing and fluid ports floating in mid-air.
2025-12-30 Implement Hexagonal Cartridge Stack with Potted Kelvin Carrier
    - Refactored cartridge stack components to Hexagonal geometry (60mm diameter).
    - Implemented `PCB_Kelvin_Insert` with central potting puck, mesh, and silver ribbon electrodes.
    - Updated `Carrier_Frame_Hex` to house the rectangular PCB insert.
    - Updated `Housing_Lid_Reader` with hexagonal socket for self-indexing and 5-pin linear pogo layout.
    - Added `O_Ring_Inner` modules for sealing the potting puck.
    - Corrected assembly logic for Top-Down pogo pin access.
2026-01-01 minor update, lots of little changes,
2026-01-08 Add KiCad specific patterns to .gitignore
2026-01-09 Refactor Sentinel Nanopore Reader OpenSCAD code into modular files
    This change breaks down the monolithic `sentinel_nanopore_reader.scad` file into smaller, more manageable modules:
    - `constants.scad`: Global variables and BOSL2 includes.
    - `modules/common.scad`: Shared utility modules.
    - `modules/cartridge.scad`: Cartridge stack components.
    - `modules/housing_pump.scad`: Pump module housing.
    - `modules/housing_reader.scad`: Reader module housing.
2026-01-15 Fix Cartridge Stack colors and attachments
    Refactored `PCB_Active_Stack_3D` and `Gasket_Low_Dead_Volume_3D` to use the BOSL2 `attachable` wrapper correctly.
    - `PCB_Active_Stack_3D`: Uses `attachable` to define a phantom attachment geometry while rendering only the internal PCB components. This prevents a solid cylinder from obscuring the components and r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
    - `Gasket_Low_Dead_Volume_3D`: Moves the `children()` call outside the internal `diff` block, placing it as a direct child of `attachable`. This ensures robust attachment propagation and prevents unn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
    - Restores proper color visibility for the Cartridge Stack ass
2026-01-18 Update PCB position to be on top of the lid and remove mounting holes
2026-01-18 Fix floating PCB standoffs in Housing_Lid_Reader
    - Moved standoffs from rim level (-lid_thick) to ceiling level (-ceiling_thick).
    - Removed rotation to ensure correct downward orientation from ceiling.
    - Fixed screw hole attachment to properly cut into the standoff from the bottom.
2026-01-18 Refactor PCB_Active_Stack_3D to remove union wrapper
    Replaced the explicit union() around Nanopore_Carrier and PCB_Rigid_Active with a helper module PCB_Active_Stack_Parts. This allows the two boards to exist as separate objects in the OpenSCAD tree wh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
2026-01-18 Fix Pump Module port penetration depth
    Increased the cut depth for DIN, USB-C, and Barrel Jack ports on the Housing_Pump_Case from wall*3 to wall*10. This ensures the cutouts fully penetrate the thick wall of the housing, resolving the is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
2026-01-18 Restore gasket verification tests
    - Restored `tests/test_gasket_plan.scad` for visual verification.
    - Restored `tests/verify_gasket_integration.js` for targeted DXF rendering checks.
2026-01-29 Fix export script Windows compatibility and VFS paths
    Updated `scripts/export_all.js` to force forward slashes for Virtual File System paths, resolving `Can't open include file` errors on Windows.
    The script now correctly mounts `BOSL2` and `modules` into the WASM instance regardless of the host OS separator.
    Also confirmed redundant `projection()` calls were removed from `sentinel_nanopore_reader.scad` in the previous step.
2026-01-31 Fix Torque Cap ribs/ceiling and Main PCB position
    - Remove ribs from finger slots in Torque Cap to prevent interference.
    - Add ceiling to Torque Cap by limiting internal clearance cut height.
    - Move Main Reader PCB to internal position (underside of lid) to fix visual protrusion.
2026-01-31 Rotate pump ports to horizontal alignment and fix blue tube routing
    - Modified `modules/housing_pump.scad`: Changed port generation loop to use `x_pos` (horizontal) instead of `y_pos` (vertical) on Left/Right faces, aligning them at Y=+/-20mm.
    - Modified `sentinel_nanopore_reader.scad`: Updated the "DeepSkyBlue" external tubing visualization to route around the back of the device, preventing clipping through the housing case.
    - Verified changes by compilation and code review.
2026-02-01 Refine Plate 3 cutout to strictly conform to PCB component layout
    Replaces the generic convex hull cutout in `Plate_3_Top_Hex` with a precise union of hulls targeting the Top OpAmp and Bottom Component Cluster (JST, OpAmp 2, Filters). This ensures the cutout "hugs"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
    Calculated component bounds from `PCB_Rigid_Active` and applied ~1mm clearance.
2026-02-01 Update PCB pad visualization to Gold pads with Silver ribbons
    - Updated `PCB_Rigid_Active` in `modules/cartridge.scad`:
    - Reverted bottom pads base color to Gold (all 4 pads are now Gold).
    - Added a 0.8mm wide Silver ribbon strip to each of the 4 pads.
    - Adjusted Z-offsets of the ribbons (+0.06 for top, -0.06 for bottom) to ensure they render visibly on top of the pads.
2026-02-01 Add missing fluid and electrode ports to Plate_3_Top_Hex
    This change adds missing pass-through holes to the `Plate_3_Top_Hex` module (often referred to as the "Top Cap" of the stack).
    - Added clearance holes for `angle_fluid_in_bot` and `angle_fluid_out_bot` to match the 4-port pattern found on other stack layers.
    - Added a clearance hole for `angle_elec_cis` (Top Electrode) which was previously missing in the Hex version but present in the legacy Round version.
    This addresses the issue where the top plate had an incomplete hole pattern relative to the rest of the cartridge stack. Note: Bolt holes are explicitly excluded as the stack does not use bolts.
2026-02-19 Reduce Torque Cap size and add ergonomic grips
    - Updated `constants.scad`: Reduced `neck_od` from 90mm to 75mm to shrink the overall cap and thread size.
    - Updated `modules/torque_cap.scad`:
    - Changed `Torque_Cap_Outer` to use `rounding=2` (2mm fillet) on both top and bottom edges.
    - Added 12 vertical recessed grip indentations (cylindrical cuts) to the outer perimeter, offset by 15 degrees to interleave with existing finger slots.
    - Verified changes using a simplified render test script (`test_render_single.js` with `openscad-wasm`).
2026-02-19 updated cap rib finger height
2026-02-20 Fix Housing_Reader_Lid_STL export failure due to 2D/3D mixing.
    Replaced 2D `circle` subtraction with 3D `cylinder` in `Housing_Lid_Reader` to resolve "Mixing 2D and 3D objects" warning which caused the main body to disappear.
    Added 0.1mm overlap to PCB Mounts and Indexing Lip to resolve CGAL assertion violations during union operations.
    Verified with regression script `reproduce_issue.js` showing successful generation and reasonable file size (2.5MB).
2026-03-01 Update Torque_Cap_Inner retention flange to be rounded and protrude 0.2mm
    - Changed the `cyl` diameter for the retention flange from `neck_od + 8` to `neck_od + 6.4`.
    - Added `rounding=1` to the `cyl` module to make the flange edges round.
    - These changes ensure the flange only protrudes about 0.2mm radially past the torque triangles, matching the design request.
2026-03-04 fix: thicken pump lid to support deeper foot dimples
    - Added `pump_lid_thick` constant (`wall + 2`) to ensure 7mm total thickness for the pump lid.
    - Modified `modules/housing_pump.scad` to use the thicker `pump_lid_thick` so the 4mm deep dimple doesn't poke out or get too thin.
    - Updated main assembly translations (`test_render.scad`, `test_verify.scad`, `sentinel_nanopore_reader.scad`) to use `pump_lid_thick` instead of `wall` for correct stacking height calculations.
2026-03-13 updated reader
2026-03-15 fix: Resolve remaining nonplanar face export errors in pump case
    - Adjusts the `Housing_Pump_Case` handle `path_sweep` to fully penetrate the housing wall (`translate([0, 0, -1])`) and sets a lower polygon count (`$fn=16`) to mitigate "PolySet has nonplanar faces"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
    - Adds `overlap=0.1` to `attach()` boundaries (LEFT, RIGHT, TOP, FRONT, BACK) to resolve perfectly coincident vertices.
    - Lowers poly counts on edge components like Lid Mounts (`$fn=16`) to simplify intersection mesh.
2026-03-20 Revert "feat: Ratchet-style torque limiter flex arm"
2026-03-27 docs: add 1/8" hose barb bulkhead luer to BOM
    Added Item 96550 / Ark-Plas LJX39-PP0 (1/8" Hose Barb x Female Threaded Natural Polypropylene Bulkhead Luer) to the Bill of Materials table in BOM.md.
2026-03-28 Enlarge fluid routing holes on reader lid top to 10mm

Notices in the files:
README.md:
- [LICENSE](LICENSE): CC0 1.0 Universal (CC0-1.0) Public Domain Dedication.
